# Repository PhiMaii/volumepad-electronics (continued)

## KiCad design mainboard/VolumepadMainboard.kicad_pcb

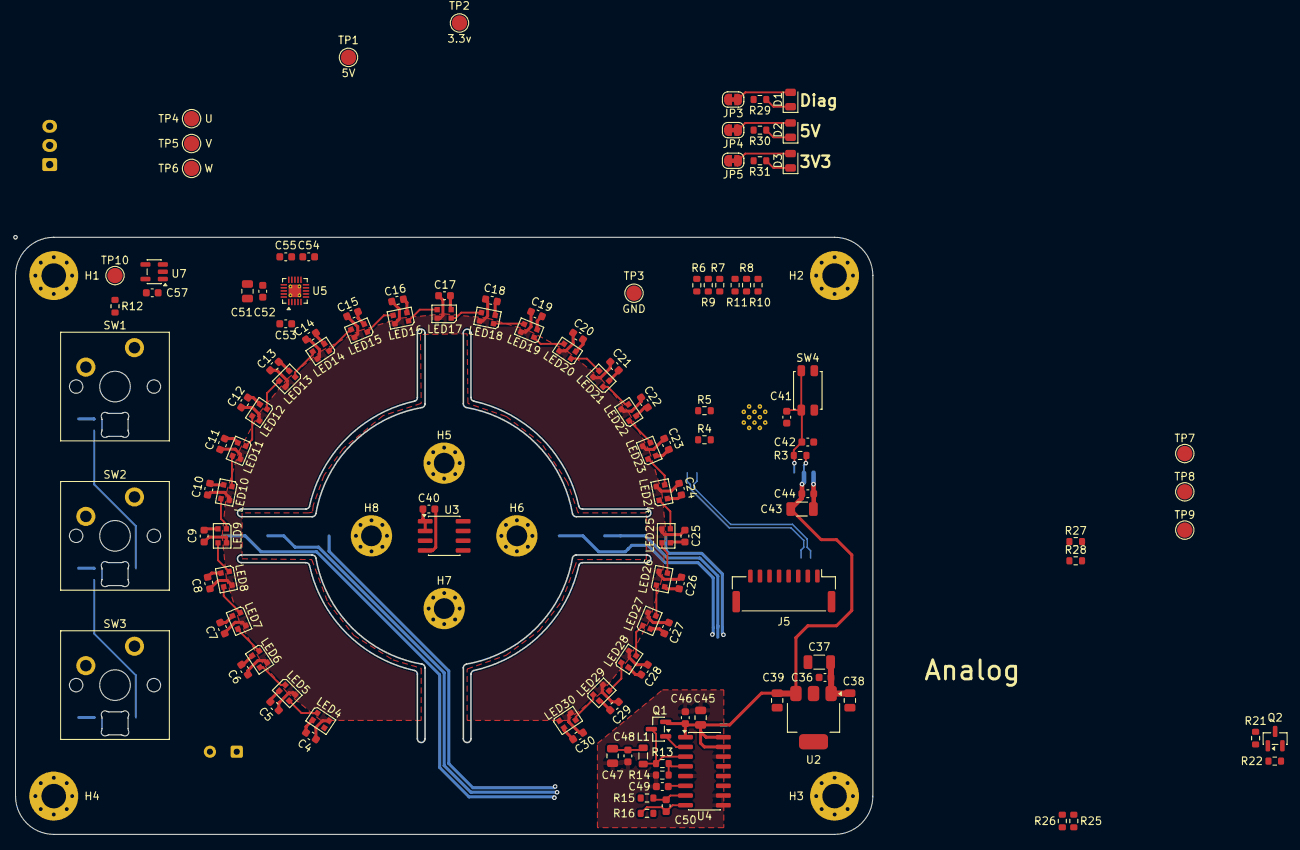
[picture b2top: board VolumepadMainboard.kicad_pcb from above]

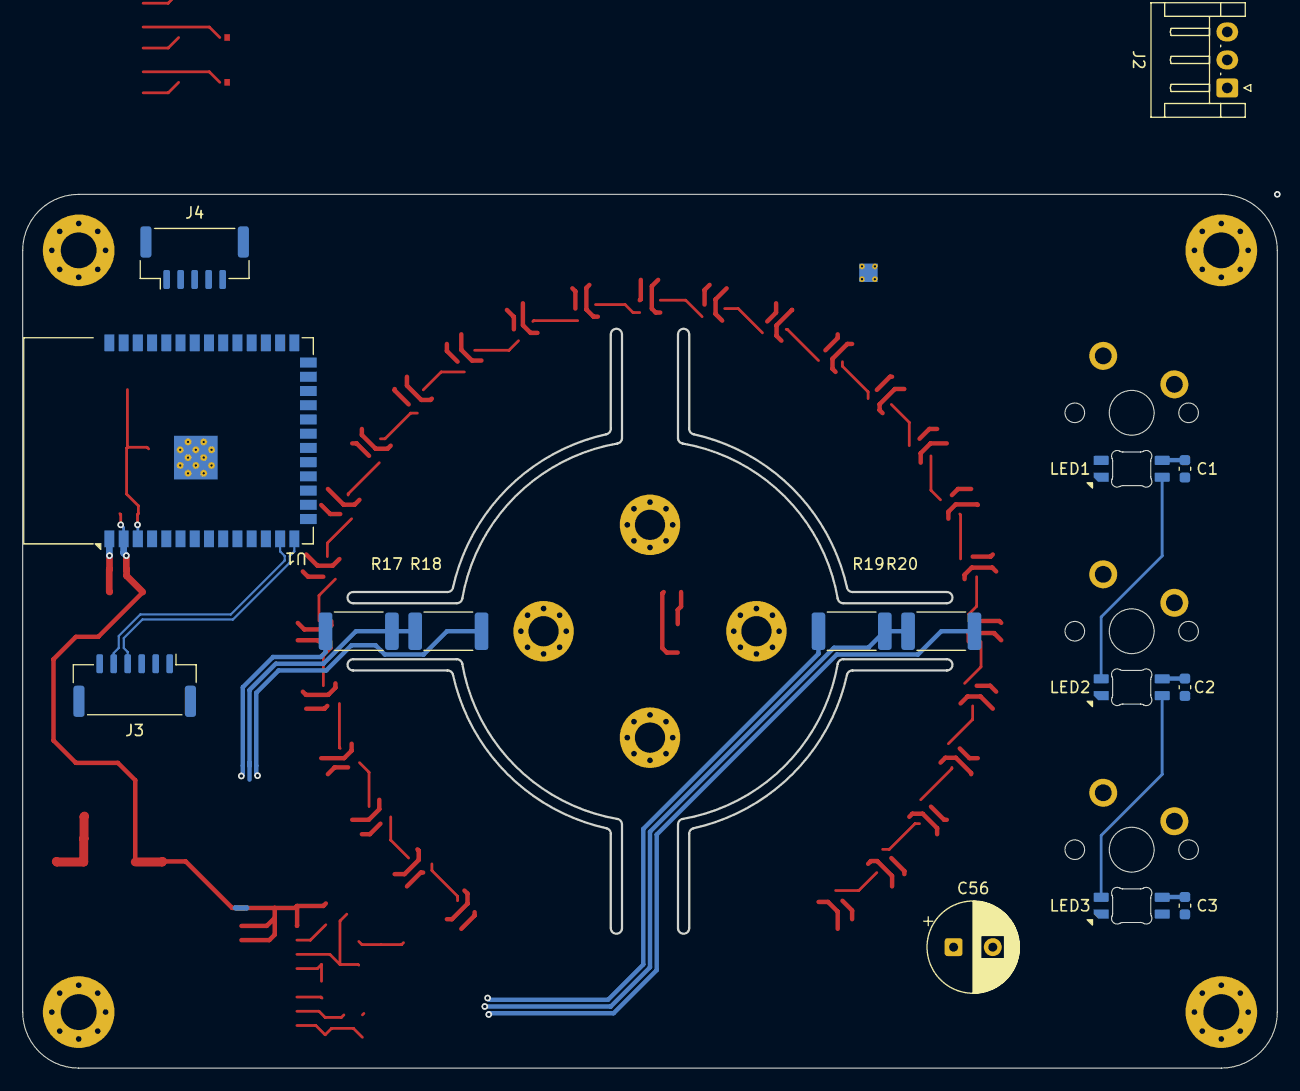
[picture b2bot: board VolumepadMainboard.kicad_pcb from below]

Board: 2 copper layers, 112.0 x 78.0 mm, 151 parts (16 on the bottom side), 86 nets.

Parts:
C1, C2, C3, C4, C5, C6, C7, C8, C9, C10, C11, C12, C13, C14, C15, C16, C17, C18, C19, C20, C21, C22, C23, C24, C25, C26, C27, C28, C29, C30, C40, C41, C44, C46, C48, C49, C50, C52, C53, C54, C55, C57: 0.1uF; C_0603_1608Metric
C36: 100nF; C_0603_1608Metric
C37: 47uF; C_1206_3216Metric
C38, C39, C45, C47: 10uF; C_0805_2012Metric
C42: 1uF; C_0603_1608Metric
C43: 22uF; C_1206_3216Metric
C51: 22uF; C_0805_2012Metric
C56: 1mF; CP_Radial_D8.0mm_P3.50mm
D1: ORANGE; LED_0805_2012Metric
D2: GREEN; LED_0805_2012Metric
D3: BLUE; LED_0805_2012Metric
H1, H3, H4: PCB_MountingHole; MountingHole_3.2mm_M3_Pad_Via
H2: M2.5_PCB_MountingHole; MountingHole_3.2mm_M3_Pad_Via
H5, H6, H7, H8: Motor_MountingHole; MountingHole_2.7mm_M2.5_Pad_Via
J2: BLDC; JST_EH_S3B-EH_1x03_P2.50mm_Horizontal
J3: USB_Extension_Board; JST_GH_BM06B-GHS-TBT_1x06-1MP_P1.25mm_Vertical
J4: Touch_Extension_Board; JST_GH_BM05B-GHS-TBT_1x05-1MP_P1.25mm_Vertical
J5: Display_Connector; JST_GH_BM08B-GHS-TBT_1x08-1MP_P1.25mm_Vertical
JP3, JP4, JP5: Standby Jumper; SolderJumper-2_P1.3mm_Bridged_RoundedPad1.0x1.5mm
L1: 3.3uH; L_0805_2012Metric
LED1, LED2, LED3: MX_SK6812MINI-E; LED_MX_6028R
LED4, LED5, LED6, LED7, LED8, LED9, LED10, LED11, LED12, LED13, LED14, LED15, LED16, LED17, LED18, LED19, LED20, LED21, LED22, LED23, LED24, LED25, LED26, LED27, LED28, LED29, LED30: WS2812B-2020; LED_WS2812B-2020_PLCC4_2.0x2.0mm
NT1: NetTie_2; NetTie-2_SMD_Pad0.5mm
Q1: MMBT4403; SOT-23
Q2: 2N7002; SOT-23
R3, R6, R7, R8, R9, R10, R11, R13: 10k; R_0603_1608Metric
R4, R5, R25, R26, R30: 2.2k; R_0603_1608Metric
R12, R27, R28: 33; R_0603_1608Metric
R14: 8.2k; R_0603_1608Metric
R15, R16: 100; R_0603_1608Metric
R17, R18, R19, R20: 330; R_2512_6332Metric
R21: 220; R_0603_1608Metric
R22: 100K; R_0603_1608Metric
R29: 330; R_0603_1608Metric
R31: 1k; R_0603_1608Metric
SW1, SW2, SW3: SW_Push; SW_Cherry_MX_PCB_1.00u
SW4: SW_Push; SW_SPST_EVQP2_MiddlePushTravel_H2.5mm
TP1: 5V; TestPoint_Pad_D2.0mm
TP2: 3.3v; TestPoint_Pad_D2.0mm
TP3: GND; TestPoint_Pad_D2.0mm
TP4: U; TestPoint_Pad_D2.0mm
TP5: V; TestPoint_Pad_D2.0mm
TP6: W; TestPoint_Pad_D2.0mm
TP7: CSN; TestPoint_Pad_D2.0mm
TP8: CLK; TestPoint_Pad_D2.0mm
TP9: DO; TestPoint_Pad_D2.0mm
TP10: LED; TestPoint_Pad_D2.0mm
U1: ESP32-S3-WROOM-1
U2: AP2114HA-3.3; SOT-223-3_TabPin2
U3: MT6701-CT; SOIC-8_3.9x4.9mm_P1.27mm
U4: HX711; SOIC-16_3.9x9.9mm_P1.27mm
U5: TMC6300; QFN-20-1EP_3x3mm_P0.4mm_EP1.65x1.65mm_ThermalVias
U7: SN74LV1T34DBV; SOT-23-5

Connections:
+3V3: C39.1, C40.1, C43.1, C44.1, C45.1, C46.1, C54.1, J4.1, J5.7, JP5.2 (B), Q1.2 (E), R3.1, R4.1, R5.2, R25.2, R26.2, TP2.1, U1.2 (3V3), U2.3 (VO), U3.1 (VDD), U3.2 (MODE), U4.1 (VSUP), U4.15 (RATE), U4.16 (DVDD), U5.11 (VIO/~STDBY)
+5V: C1.1, C2.1, C3.1, C4.1, C5.1, C6.1, C7.1, C8.1, C9.1, C10.1, C11.1, C12.1, C13.1, C14.1, C15.1, C16.1, C17.1, C18.1, C19.1, C20.1, C21.1, C22.1, C23.1, C24.1, C25.1, C26.1, C27.1, C28.1, C29.1, C30.1, C36.1, C37.1, C38.1, C51.1, C52.1, C53.1, C56.1, C57.1, J3.1, J3.2, JP4.2 (B), LED1.1 (VDD), LED2.1 (VDD), LED3.1 (VDD), LED4.4 (VDD), LED5.4 (VDD), LED6.4 (VDD), LED7.4 (VDD), LED8.4 (VDD), LED9.4 (VDD), LED10.4 (VDD), LED11.4 (VDD), LED12.4 (VDD), LED13.4 (VDD), LED14.4 (VDD), LED15.4 (VDD), LED16.4 (VDD), LED17.4 (VDD), LED18.4 (VDD), LED19.4 (VDD), LED20.4 (VDD), LED21.4 (VDD), LED22.4 (VDD), LED23.4 (VDD), LED24.4 (VDD), LED25.4 (VDD), LED26.4 (VDD), LED27.4 (VDD), LED28.4 (VDD), LED29.4 (VDD), LED30.4 (VDD), TP1.1, U2.1 (VI), U5.18 (VS), U7.5 (VCC)
Aux_USB_D+: J3.4, U1.14 (USB_D+)
Aux_USB_D-: J3.5, U1.13 (USB_D-)
BUTTON_1: SW1.1, U1.39 (IO1)
BUTTON_2: SW2.1, U1.38 (IO2)
BUTTON_3: SW3.1, U1.15 (IO3)
ESP32_EN: C41.2, C42.1, R3.2, SW4.2, U1.3 (EN)
GND: C1.2, C2.2, C3.2, C4.2, C5.2, C6.2, C7.2, C8.2, C9.2, C10.2, C11.2, C12.2, C13.2, C14.2, C15.2, C16.2, C17.2, C18.2, C19.2, C20.2, C21.2, C22.2, C23.2, C24.2, C25.2, C26.2, C27.2, C28.2, C29.2, C30.2, C36.2, C37.2, C38.2, C39.2, C40.2, C41.1, C42.2, C43.2, C44.2, C51.2, C52.2, C54.2, C55.2, C56.2, C57.2, H1.1, H2.1, H3.1, H4.1, H5.1, H6.1, H7.1, H8.1, J3.3, J3.6, J4.2, J5.8, LED1.4 (VSS), LED2.4 (VSS), LED3.4 (VSS), LED4.2 (VSS), LED5.2 (VSS), LED6.2 (VSS), LED7.2 (VSS), LED8.2 (VSS), LED9.2 (VSS), LED10.2 (VSS), LED11.2 (VSS), LED12.2 (VSS), LED13.2 (VSS), LED14.2 (VSS), LED15.2 (VSS), LED16.2 (VSS), LED17.2 (VSS), LED18.2 (VSS), LED19.2 (VSS), LED20.2 (VSS), LED21.2 (VSS), LED22.2 (VSS), LED23.2 (VSS), LED24.2 (VSS), LED25.2 (VSS), LED26.2 (VSS), LED27.2 (VSS), LED28.2 (VSS), LED29.2 (VSS), LED30.2 (VSS), NT1.2, Q2.2 (S), R6.2, R7.2, R8.2, R9.2, R10.2, R11.2, R22.1, R29.2, R30.2, R31.2, SW1.2, SW2.2, SW3.2, SW4.1, TP3.1, U1.1 (GND), U1.40 (GND), U1.41 (GND), U2.2 (GND), U3.4 (GND), U5.8 (GND), U5.9 (GND), U5.14 (GND), U5.16 (BRUV), U5.20 (BRW), U7.3 (GND)
GNDA: C45.2, C46.2, C47.2, C48.2, C49.1, NT1.1, R14.2, R18.2, R20.1, U4.5 (AGND), U4.9 (INB-), U4.10 (INB+), U4.14 (XI)
LCD_BL_BRIGHTNESS: R21.1, U1.23 (IO21)
LCD_CS: J5.2, U1.18 (IO10)
LCD_DC: J5.3, U1.21 (IO13)
LCD_MOSI: R27.2, U1.19 (IO11)
LCD_RST: J5.4, U1.22 (IO14)
LCD_SCK: R5.1, R28.2, TP8.1, U1.20 (IO12), U3.7 (B/V/SCL/CLK)
LED_DATA_3V3: U1.10 (IO17), U7.2 (A)
LED_DATA_5V: R12.1, TP10.1, U7.4 (Y)
LED_DATA_5V_AFTER_KEYS: LED3.2 (DOUT), LED4.3 (DIN)
MAG_CSN: TP7.1, U1.31 (IO38), U3.8 (Z/W/CSN)
MAG_DO: R4.2, TP9.1, U1.17 (IO9), U3.6 (A/U/SDA/DO)
MOTOR_DIAG: JP3.2 (B), U1.11 (IO18), U5.12 (DIAG)
MOTOR_UH: R6.1, U1.28 (IO35), U5.3 (UH)
MOTOR_UL: R9.1, U1.29 (IO36), U5.6 (UL)
MOTOR_VH: R7.1, U1.30 (IO37), U5.4 (VH)
MOTOR_VL: R11.1, U1.32 (IO39), U5.10 (VL)
MOTOR_WH: R8.1, U1.33 (IO40), U5.5 (WH)
MOTOR_WL: R10.1, U1.34 (IO41), U5.7 (WL)
unnamed: D1.2 (A), JP3.1 (A)
unnamed: D1.1 (K), R29.1
unnamed: D2.2 (A), JP4.1 (A)
unnamed: D2.1 (K), R30.1
unnamed: D3.2 (A), JP5.1 (A)
unnamed: D3.1 (K), R31.1
unnamed: J2.1, TP6.1, U5.1 (W)
unnamed: J2.2, TP5.1, U5.17 (V)
unnamed: J2.3, TP4.1, U5.15 (U)
unnamed: J5.1, Q2.3 (D)
unnamed: J5.5, R27.1
unnamed: J5.6, R28.1
unnamed: LED1.3 (DIN), R12.2
unnamed: LED1.2 (DOUT), LED2.3 (DIN)
unnamed: LED2.2 (DOUT), LED3.3 (DIN)
unnamed: LED4.1 (DOUT), LED5.3 (DIN)
unnamed: LED5.1 (DOUT), LED6.3 (DIN)
unnamed: LED6.1 (DOUT), LED7.3 (DIN)
unnamed: LED7.1 (DOUT), LED8.3 (DIN)
unnamed: LED8.1 (DOUT), LED9.3 (DIN)
unnamed: LED9.1 (DOUT), LED10.3 (DIN)
unnamed: LED10.1 (DOUT), LED11.3 (DIN)
unnamed: LED11.1 (DOUT), LED12.3 (DIN)
unnamed: LED12.1 (DOUT), LED13.3 (DIN)
unnamed: LED13.1 (DOUT), LED14.3 (DIN)
unnamed: LED14.1 (DOUT), LED15.3 (DIN)
unnamed: LED15.1 (DOUT), LED16.3 (DIN)
unnamed: LED16.1 (DOUT), LED17.3 (DIN)
unnamed: LED17.1 (DOUT), LED18.3 (DIN)
unnamed: LED18.1 (DOUT), LED19.3 (DIN)
unnamed: LED19.1 (DOUT), LED20.3 (DIN)
unnamed: LED20.1 (DOUT), LED21.3 (DIN)
unnamed: LED21.1 (DOUT), LED22.3 (DIN)
unnamed: LED22.1 (DOUT), LED23.3 (DIN)
unnamed: LED23.1 (DOUT), LED24.3 (DIN)
unnamed: LED24.1 (DOUT), LED25.3 (DIN)
unnamed: LED25.1 (DOUT), LED26.3 (DIN)
unnamed: LED26.1 (DOUT), LED27.3 (DIN)
unnamed: LED27.1 (DOUT), LED28.3 (DIN)
unnamed: LED28.1 (DOUT), LED29.3 (DIN)
unnamed: LED29.1 (DOUT), LED30.3 (DIN)
unnamed: Q1.1 (B), U4.2 (BASE)
unnamed: L1.1, Q1.3 (C), R13.1, U4.3 (AVDD)
unnamed: Q2.1 (G), R21.2, R22.2
unnamed: C50.1, R16.2, U4.8 (INA+)
unnamed: C50.2, R15.1, U4.7 (INA-)
unnamed: C49.2, U4.6 (VBG)
unnamed: R13.2, R14.1, U4.4 (VFB)
unnamed: C55.1, U5.13 (1V8OUT)
unnamed: C53.2, U5.2 (VCP)
Peripheral_INT_Touch: J4.5, U1.5 (IO5)
Peripheral_SCL: J4.3, R25.1, U1.6 (IO6)
Peripheral_SDA: J4.4, R26.1, U1.7 (IO7)
STRAIN_DO: U1.12 (IO8), U4.12 (DOUT)
STRAIN_E+: C47.1, C48.1, L1.2, R17.1, R19.2
STRAIN_S+: R16.1, R17.2, R18.1
STRAIN_S-: R15.2, R19.1, R20.2
STRAIN_SCK: U1.4 (IO4), U4.11 (PD_SCK)

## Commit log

2026-02-23 Setup folder structure
2026-02-23 Updated .gitignore
2026-02-23 Migrated current version of mainboard PCB to git repo
2026-02-23 Created touchBoard project
2026-02-23 Created USBHubBoard project
2026-02-23 Removed the onboard USB-C plug and added a display connector
2026-03-22 Rearranged LEDs
2026-04-03 Moved general docs to the global docs folder while keeping the project internal docs located here
2026-04-03 Add initial README for VolumePad Electronics project
2026-06-04 Initial KiCad project commit
2026-06-04 Updated footprints to inclue 3d models for the simulation
2026-06-07 Exported first BOM csv to test with LCSC
2026-06-07 Started adding LCSC part numbers to make ordering the parts easier
2026-06-07 Added folder for 3d models for the 3D pcb viewer
2026-06-07 Move KiCad project into pcb folder
2026-06-07 Add KiBot automation
2026-06-07 Use KiCad 10 for KiBot workflow
2026-06-07 Added Readme.md file with documentation and key features
